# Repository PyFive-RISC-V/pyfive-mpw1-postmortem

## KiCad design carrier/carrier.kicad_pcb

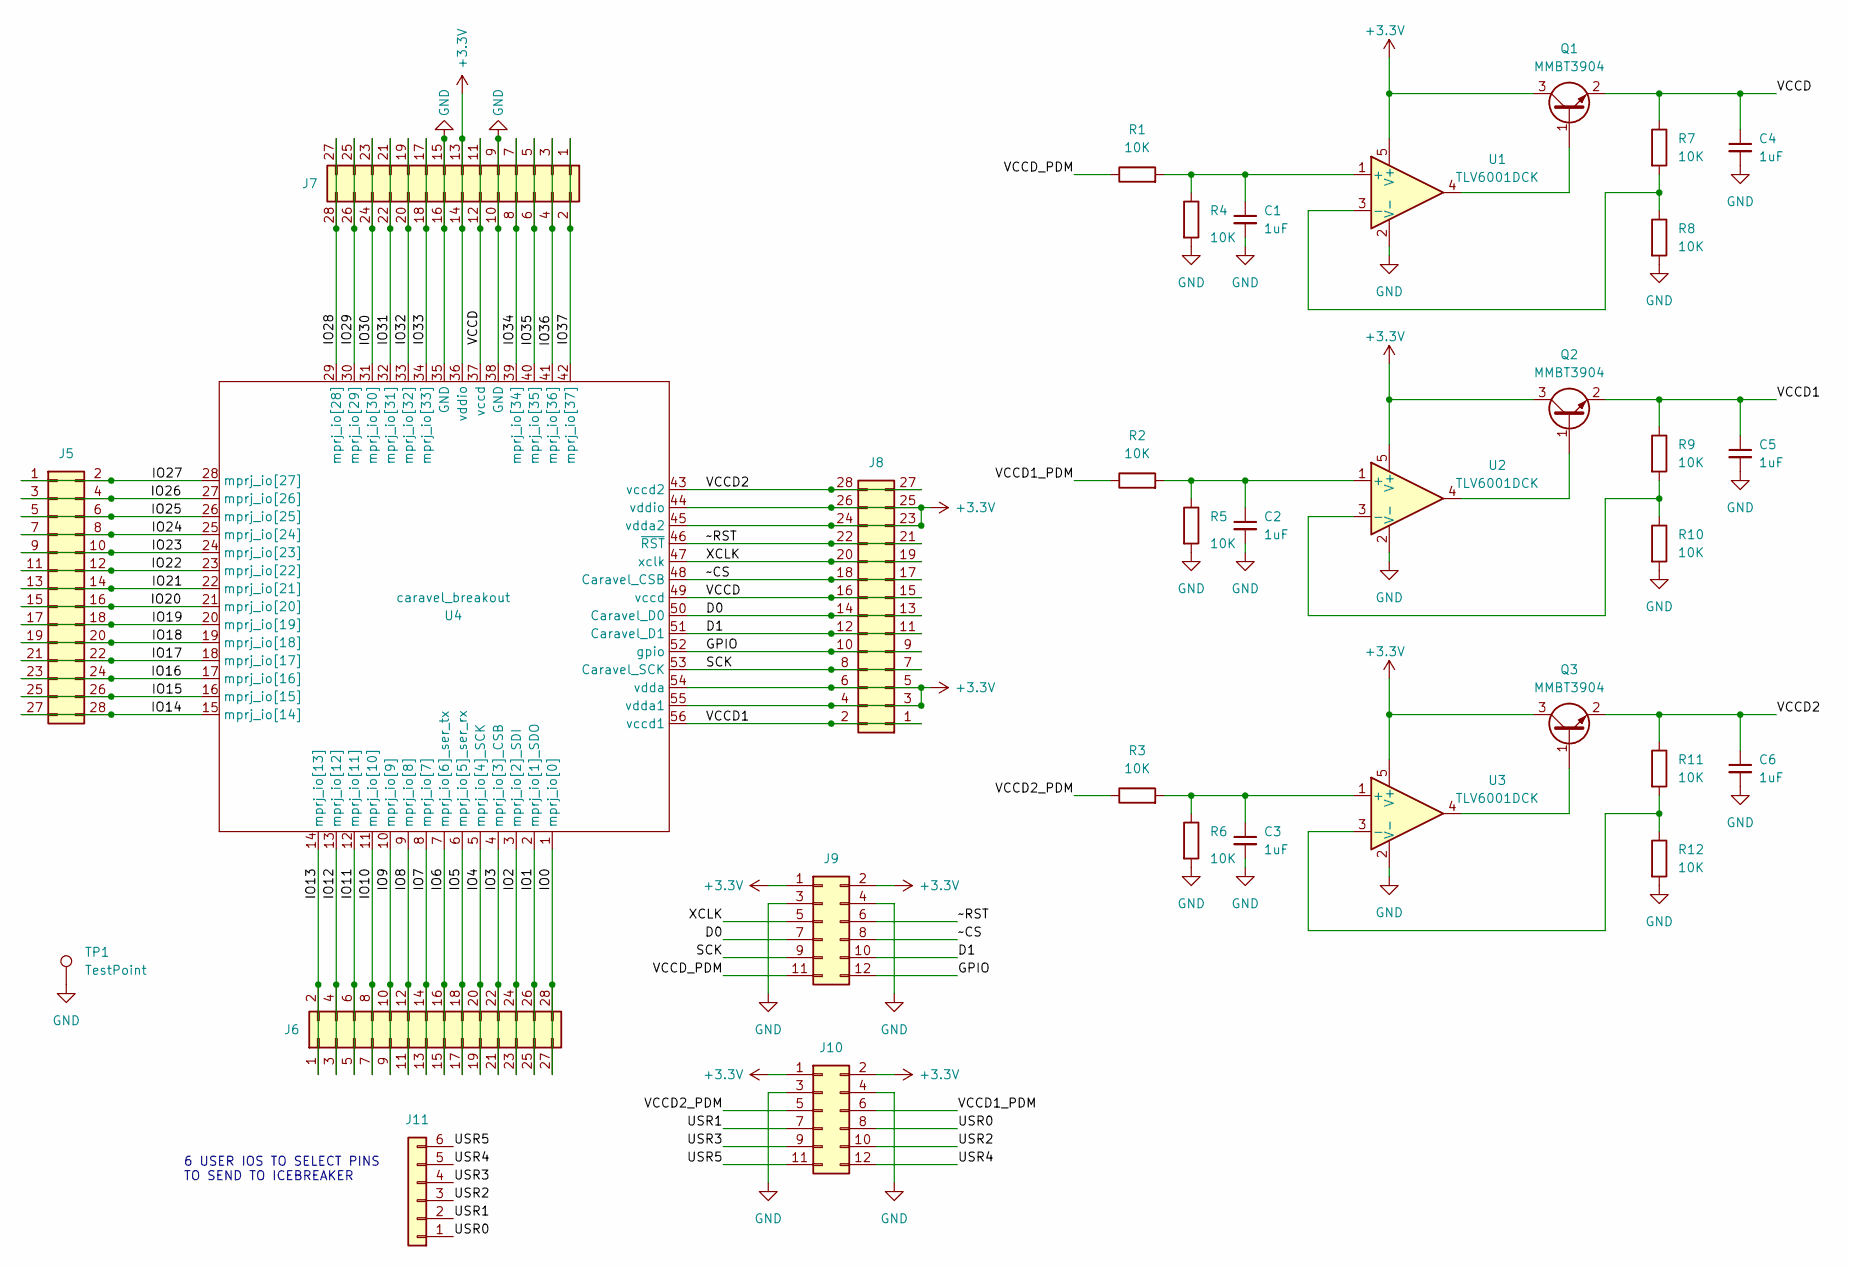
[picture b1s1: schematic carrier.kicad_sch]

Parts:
C1, C2, C3, C4, C5, C6: 1uF; C_0402_1005Metric
J5, J6, J7, J8: Conn_02x14_Odd_Even; PinHeader_2x14_P2.54mm_Vertical
J9, J10: Conn_02x06_Odd_Even; PinHeader_2x06_P2.54mm_Horizontal
J11: Conn_01x06; PinHeader_1x06_P2.54mm_Vertical
Q1, Q2, Q3: MMBT3904; SOT-23
R1, R2, R3, R4, R5, R6, R7, R8, R9, R10, R11, R12: 10K; R_0402_1005Metric
TP1: TestPoint; TestPoint_Keystone_5005-5009_Compact
U1, U2, U3: TLV6001DCK; SOT-353_SC-70-5
U4: caravel_breakout; caravel_breakout_flexy

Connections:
+3V3: J7.13, J7.14, J8.3, J8.4, J8.5, J8.6, J8.23, J8.24, J8.25, J8.26, J9.1, J9.2, J10.1, J10.2, Q1.3 (C), Q2.3 (C), Q3.3 (C), U1.5 (V+), U2.5 (V+), U3.5 (V+), U4.36 (vddio), U4.44 (vddio), U4.45 (vdda2), U4.54 (vdda), U4.55 (vdda1)
/D0: J8.13, J8.14, J9.7, U4.50 (Caravel_D0)
/D1: J8.11, J8.12, J9.10, U4.51 (Caravel_D1)
/GPIO: J8.9, J8.10, J9.12, U4.52 (gpio)
/IO0: J6.27, J6.28, U4.1 (mprj_io[0])
/IO1: J6.25, J6.26, U4.2 (mprj_io[1]_SDO)
/IO2: J6.23, J6.24, U4.3 (mprj_io[2]_SDI)
/IO3: J6.21, J6.22, U4.4 (mprj_io[3]_CSB)
/IO4: J6.19, J6.20, U4.5 (mprj_io[4]_SCK)
/IO5: J6.17, J6.18, U4.6 (mprj_io[5]_ser_rx)
/IO6: J6.15, J6.16, U4.7 (mprj_io[6]_ser_tx)
/IO7: J6.13, J6.14, U4.8 (mprj_io[7])
/IO8: J6.11, J6.12, U4.9 (mprj_io[8])
/IO9: J6.9, J6.10, U4.10 (mprj_io[9])
/IO10: J6.7, J6.8, U4.11 (mprj_io[10])
/IO11: J6.5, J6.6, U4.12 (mprj_io[11])
/IO12: J6.3, J6.4, U4.13 (mprj_io[12])
/IO13: J6.1, J6.2, U4.14 (mprj_io[13])
/IO14: J5.27, J5.28, U4.15 (mprj_io[14])
/IO15: J5.25, J5.26, U4.16 (mprj_io[15])
/IO16: J5.23, J5.24, U4.17 (mprj_io[16])
/IO17: J5.21, J5.22, U4.18 (mprj_io[17])
/IO18: J5.19, J5.20, U4.19 (mprj_io[18])
/IO19: J5.17, J5.18, U4.20 (mprj_io[19])
/IO20: J5.15, J5.16, U4.21 (mprj_io[20])
/IO21: J5.13, J5.14, U4.22 (mprj_io[21])
/IO22: J5.11, J5.12, U4.23 (mprj_io[22])
/IO23: J5.9, J5.10, U4.24 (mprj_io[23])
/IO24: J5.7, J5.8, U4.25 (mprj_io[24])
/IO25: J5.5, J5.6, U4.26 (mprj_io[25])
/IO26: J5.3, J5.4, U4.27 (mprj_io[26])
/IO27: J5.1, J5.2, U4.28 (mprj_io[27])
/IO28: J7.27, J7.28, U4.29 (mprj_io[28])
/IO29: J7.25, J7.26, U4.30 (mprj_io[29])
/IO30: J7.23, J7.24, U4.31 (mprj_io[30])
/IO31: J7.21, J7.22, U4.32 (mprj_io[31])
/IO32: J7.19, J7.20, U4.33 (mprj_io[32])
/IO33: J7.17, J7.18, U4.34 (mprj_io[33])
/IO34: J7.7, J7.8, U4.39 (mprj_io[34])
/IO35: J7.5, J7.6, U4.40 (mprj_io[35])
/IO36: J7.3, J7.4, U4.41 (mprj_io[36])
/IO37: J7.1, J7.2, U4.42 (mprj_io[37])
/SCK: J8.7, J8.8, J9.9, U4.53 (Caravel_SCK)
/USR0: J10.8, J11.1
/USR1: J10.7, J11.2
/USR2: J10.10, J11.3
/USR3: J10.9, J11.4
/USR4: J10.12, J11.5
/USR5: J10.11, J11.6
/VCCD: C4.1, J7.11, J7.12, J8.15, J8.16, Q1.2 (E), R7.1, U4.37 (vccd), U4.49 (vccd)
/VCCD1: C5.1, J8.1, J8.2, Q2.2 (E), R9.1, U4.56 (vccd1)
/VCCD1_PDM: J10.6, R2.1
/VCCD2: C6.1, J8.27, J8.28, Q3.2 (E), R11.1, U4.43 (vccd2)
/VCCD2_PDM: J10.5, R3.1
/VCCD_PDM: J9.11, R1.1
/XCLK: J8.19, J8.20, J9.5, U4.47 (xclk)
/~CS: J8.17, J8.18, J9.8, U4.48 (Caravel_CSB)
/~RST: J8.21, J8.22, J9.6, U4.46 (~RST)
GND: C1.2, C2.2, C3.2, C4.2, C5.2, C6.2, J7.9, J7.10, J7.15, J7.16, J9.3, J9.4, J10.3, J10.4, R4.2, R5.2, R6.2, R8.2, R10.2, R12.2, TP1.1, U1.2 (V-), U2.2 (V-), U3.2 (V-), U4.35 (GND), U4.38 (GND)
unnamed: C1.1, R1.2, R4.1, U1.1 (+)
unnamed: C2.1, R2.2, R5.1, U2.1 (+)
unnamed: C3.1, R3.2, R6.1, U3.1 (+)
unnamed: Q1.1 (B), U1.4
unnamed: Q2.1 (B), U2.4
unnamed: Q3.1 (B), U3.4
unnamed: R7.2, R8.1, U1.3 (-)
unnamed: R9.2, R10.1, U2.3 (-)
unnamed: R11.2, R12.1, U3.3 (-)

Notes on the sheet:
6 USER IOS TO SELECT PINS TO SEND TO ICEBREAKER

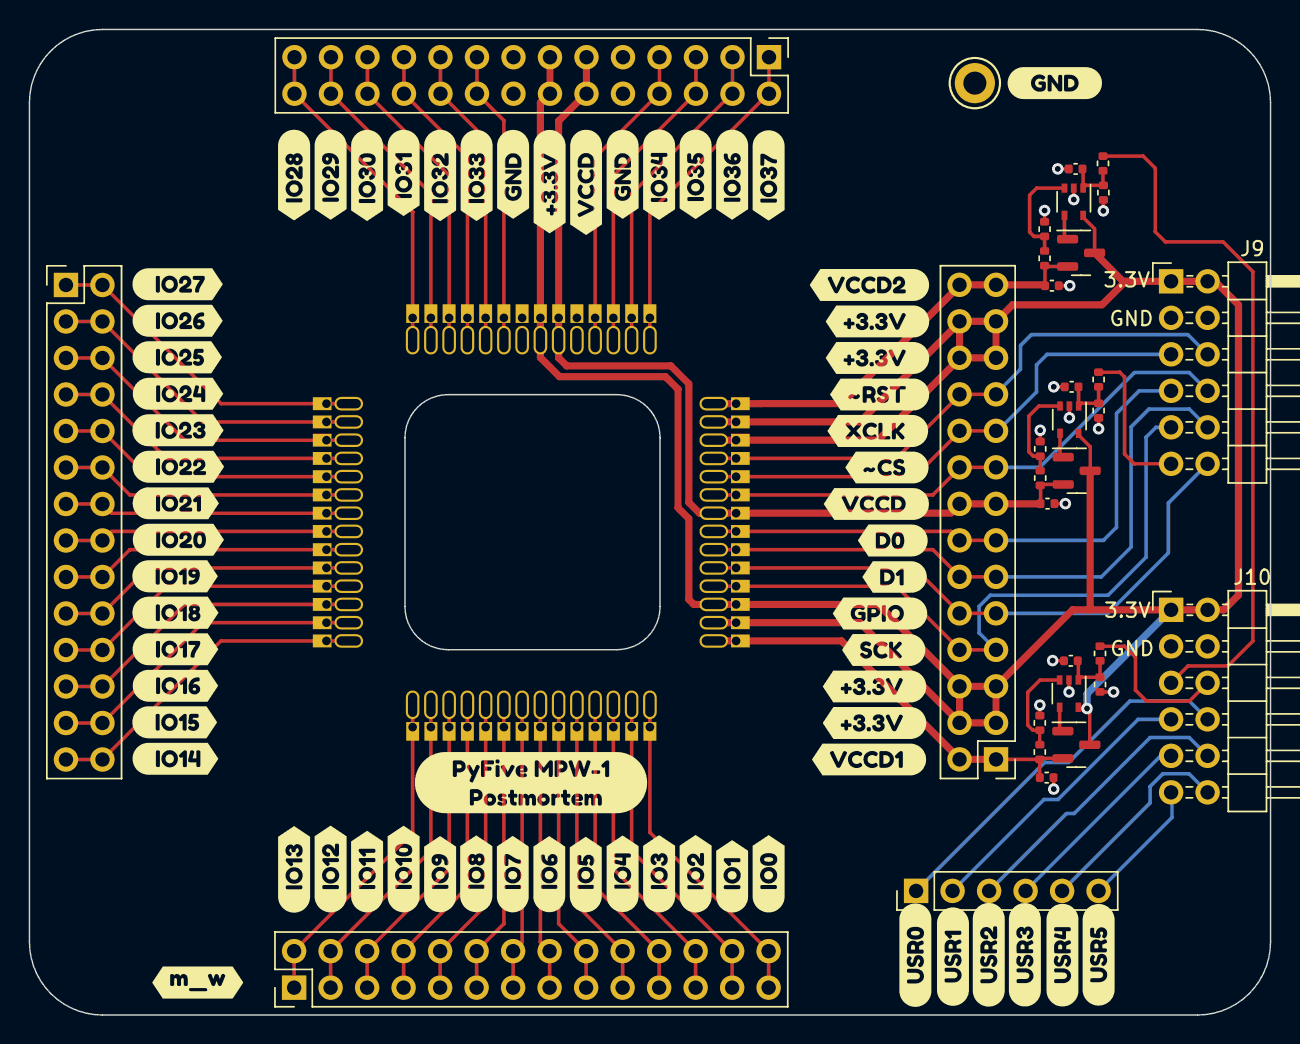
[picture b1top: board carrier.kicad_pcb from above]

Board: 2 copper layers, 86.4 x 68.6 mm, 98 parts (1 on the bottom side), 68 nets.

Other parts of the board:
kibuzzard-61D3A0A1: G***; kibuzzard-61D3A0A1
kibuzzard-61D3A0AB: G***; kibuzzard-61D3A0AB
kibuzzard-61D3A0B4: G***; kibuzzard-61D3A0B4
kibuzzard-61D3A0BC: G***; kibuzzard-61D3A0BC
kibuzzard-61D3A0C4: G***; kibuzzard-61D3A0C4
kibuzzard-61D3A0CB: G***; kibuzzard-61D3A0CB
kibuzzard-61D3A001: G***; kibuzzard-61D3A001
kibuzzard-61D3A2BD: G***; kibuzzard-61D3A2BD
kibuzzard-61D3A02C: G***; kibuzzard-61D3A02C
kibuzzard-61D3A2C5: G***; kibuzzard-61D3A2C5
kibuzzard-61D3A2CC: G***; kibuzzard-61D3A2CC
kibuzzard-61D3A2D7: G***; kibuzzard-61D3A2D7
kibuzzard-61D3A2DF: G***; kibuzzard-61D3A2DF
kibuzzard-61D3A2E7: G***; kibuzzard-61D3A2E7
kibuzzard-61D3A2F7: G***; kibuzzard-61D3A2F7
kibuzzard-61D3A2FF: G***; kibuzzard-61D3A2FF
kibuzzard-61D3A3A4: G***; kibuzzard-61D3A3A4
kibuzzard-61D3A3B7: G***; kibuzzard-61D3A3B7
kibuzzard-61D3A3D2: G***; kibuzzard-61D3A3D2
kibuzzard-61D3A04B: G***; kibuzzard-61D3A04B
kibuzzard-61D3A06E: G***; kibuzzard-61D3A06E
kibuzzard-61D3A011: G***; kibuzzard-61D3A011
kibuzzard-61D3A022: G***; kibuzzard-61D3A022
kibuzzard-61D3A32B: G***; kibuzzard-61D3A32B
kibuzzard-61D3A034: G***; kibuzzard-61D3A034
kibuzzard-61D3A34D: G***; kibuzzard-61D3A34D
kibuzzard-61D3A36A: G***; kibuzzard-61D3A36A
kibuzzard-61D3A38A: G***; kibuzzard-61D3A38A
kibuzzard-61D3A055: G***; kibuzzard-61D3A055
kibuzzard-61D3A061: G***; kibuzzard-61D3A061
kibuzzard-61D3A086: G***; kibuzzard-61D3A086
kibuzzard-61D3A092: G***; kibuzzard-61D3A092
kibuzzard-61D3A338: G***; kibuzzard-61D3A338
kibuzzard-61D3A343: G***; kibuzzard-61D3A343
kibuzzard-61D3A357: G***; kibuzzard-61D3A357
kibuzzard-61D3A360: G***; kibuzzard-61D3A360
kibuzzard-61D3A377: G***; kibuzzard-61D3A377
kibuzzard-61D3A382: G***; kibuzzard-61D3A382
kibuzzard-61D3A397: G***; kibuzzard-61D3A397
kibuzzard-61D3CE10: G***; kibuzzard-61D3CE10
kibuzzard-61D3CE89: G***; kibuzzard-61D3CE89
kibuzzard-61D39D9C: G***; kibuzzard-61D39D9C
kibuzzard-61D39DAF: G***; kibuzzard-61D39DAF
kibuzzard-61D39DC0, kibuzzard-61D39DC0#2, kibuzzard-61D39DC0#3, kibuzzard-61D39DC0#4: G***; kibuzzard-61D39DC0
kibuzzard-61D39DCB: G***; kibuzzard-61D39DCB
kibuzzard-61D39DE2: G***; kibuzzard-61D39DE2
kibuzzard-61D39DF2: G***; kibuzzard-61D39DF2
kibuzzard-61D39E00: G***; kibuzzard-61D39E00
kibuzzard-61D39E2F: G***; kibuzzard-61D39E2F
kibuzzard-61D39E13: G***; kibuzzard-61D39E13
kibuzzard-61D39E22: G***; kibuzzard-61D39E22
kibuzzard-61D39E43: G***; kibuzzard-61D39E43
kibuzzard-61D39FDA: G***; kibuzzard-61D39FDA
kibuzzard-61D39FEA: G***; kibuzzard-61D39FEA
kibuzzard-61D39FF5: G***; kibuzzard-61D39FF5
kibuzzard-61D400CC: G***; kibuzzard-61D400CC
kibuzzard-61D401EF: G***; kibuzzard-61D401EF
kibuzzard-61D401FF: G***; kibuzzard-61D401FF
kibuzzard-61D4010F: G***; kibuzzard-61D4010F
kibuzzard-61D4014A: G***; kibuzzard-61D4014A
kibuzzard-61D40135: G***; kibuzzard-61D40135
kibuzzard-61D40313: G***; kibuzzard-61D40313

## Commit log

2022-01-04 Tweaks based on tnt's feedback
    Wired GPIO to PMOD1
    Switch 6 IOs on PMOD to attach to a header
    Add GND test point
    Add alignment holes for breakout
2022-01-19 Create LICENSE
2022-02-02 Initial import of the bringup FPGA project
2022-08-16 carrier: Flexy pin version
